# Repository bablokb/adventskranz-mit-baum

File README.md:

Adventskranz mit Baumornament
=============================

In diesem Projekt geht es um einen Adventskranz aus dem 3D-Drucker.
Statt Kerzen kommen Baum-Ornamente zum Einsatz.

3D-Modelle
----------

Das Modell des Baums (`3D/Ornament.stl.gz`) ist von
<https://www.thingiverse.com/thing:2705104>. Mein Remix
(`3D/Ornament-mit-Basis.stl.gz`) fügt einen
kleinen Stamm hinzu sowie ein Loch im Boden. Das dazugehörige
OpenScad-Programm gibt es auch im Verzeichnis `3D`.
N.B: beide STL-Dateien sind mit gzip komprimiert.

Gedruckt ist das Ornament im Vasenmodus mit naturfarbenem PET. Die
Druckdauer beträgt ca. 2 Stunden pro Ornament (0.2mm Schichtdicke).

Der Kranz ist mit OpenScad entworfen und benötigt 6 Stunden Druckzeit.
Zusätzlich gibt es noch Abdeckungen für die Kabelkanäle. Davon
sind vier notwendig, eine Abdeckung hat einen passenden Ausschnitt
für die Kabelzuführung.

Die Toleranzen sind sehr gering, je nach Drucker und Material
ist hier eine Anpassung notwendig. Dank OpenScad ist das auch
ohne große Vorkenntnisse leicht möglich.

Hardware-Setup
--------------

Das Projekt verwendet diffuse 8mm Neopixels von Adafruit, siehe
<https://www.adafruit.com/product/1734>. Ähnliche LEDs gibt es
auch auf eBay. Die Ansteuerung ist i.a.R. gleich, das Pinout
aber nicht.

Jedes Pixel benötigt einen 100nF-Kondensator, das erste Pixel
zusätzlich noch einen 300 Ohm Widerstand in der Datenleitung.

Neopixel benötigen normalerweise 5V (Versorgungsspannung und auf
der Datenleitung). Bei vier Pixel funktioniert es aber i.a.R. auch
mit 3V3. Alle Details zu Neopixel gibt es in dem umfassenden
Handbuch von Adafruit
(<https://learn.adafruit.com/adafruit-neopixel-uberguide>).

Platine
-------

Im Verzeichnis `pcb` gibt es die KiCAD-Quellen für eine passende
Platine. Die Dimensionen der Platine sind exakt auf den Kranz
abgestimmt. Die Miniplatine enthält den Kondensator und den
Widerstand, wobei das Layout so ist, dass die Platine mit oder
ohne Widerstand verwendet werden kann.

Python-Quellen
--------------

Das Verzeichnis `src_python_btn` enthält ein CircuitPython-Programm für
die Steuerung. Das Programm verwendet einen Taster für das Schalten
der LEDs.

Eine Alternativimplementation ist im Verzeichnis `src_python_sr04`.
Hier kommt ein Distanz-Sensor (HC-SR04) statt des Tasters zum Einsatz.

Eine weitere Alternative ist im Verzeichnis `src_python_touch`
vorhanden. Das Beispiel verwendet die direkte Touch-Unterstützung
durch einen Pin des Mikrokontrollers.

Die vom Projekt mitgelieferten Libs sind auf dem 9.x-Stand und mit
Circuit-Python 9.2.0 mit dem Trinket-M0 getestet.

Attiny85-Quellen
----------------

Im Verzeichnis `src_attiny85` gibt es den Quellcode als C-Programm.

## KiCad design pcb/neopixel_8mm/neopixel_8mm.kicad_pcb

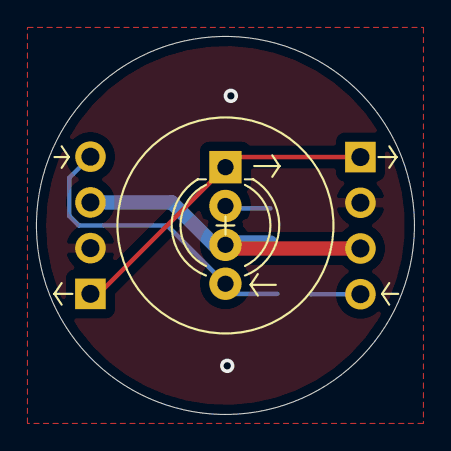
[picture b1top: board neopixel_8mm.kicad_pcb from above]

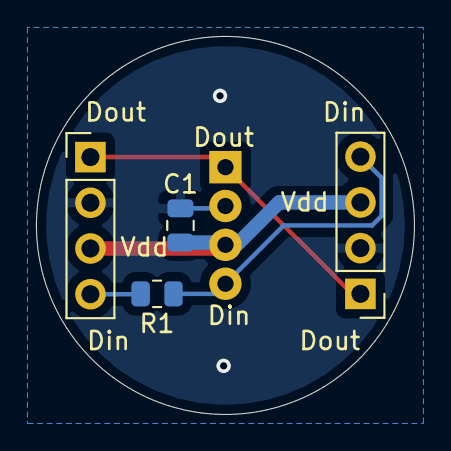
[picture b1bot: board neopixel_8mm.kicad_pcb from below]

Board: 2 copper layers, 21.0 x 21.0 mm, 5 parts (4 on the bottom side), 5 nets.

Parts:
C1: C; C_0805_2012Metric
D1: NeoPixel_THT; LED_D5.0mm-4_RGB_Wide_Pins
J1: Conn_First; PinHeader_1x04_P2.54mm_Vertical
J2: Conn_Next; PinHeader_1x04_P2.54mm_Vertical
R1: R; R_0805_2012Metric

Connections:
GND: C1.2, D1.2, J1.2, J2.2
unnamed: D1.1, J1.1, J2.1
unnamed: D1.4, J2.4, R1.1
unnamed: J1.4, R1.2
VDD: C1.1, D1.3, J1.3, J2.3

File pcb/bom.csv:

Comment,Designator,Footprint,LCSC
"100nF","C1","Capacitor_SMD:C_0805_2012Metric","C49678"
"NeoPixel_THT","D1","LED_THT:LED_D5.0mm-4_RGB_Wide_Pins",""
"Conn_First","J1","Connector_PinHeader_2.54mm:PinHeader_1x04_P2.54mm_Vertical",""
"Conn_Next","J2","Connector_PinHeader_2.54mm:PinHeader_1x04_P2.54mm_Vertical",""
"300Ω","R1","Resistor_SMD:R_0805_2012Metric","C17617"

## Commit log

2021-08-21 added vscode-files
2021-08-21 added text
2021-08-21 translated to German
2021-08-31 added some comments
2021-08-31 fixed reference to stl
2021-09-04 pack stl in zip
2021-09-04 document stl within zip
2021-09-07 added cover
2021-09-09 fixed postion of cutout on cover
2021-09-11 replaced zip-version with gzip version
2021-09-11 compress file
2021-09-11 updated project-url
2021-09-20 optimzed cover
2021-09-20 added some details
2021-09-22 updated to 7.x-library bundle
2021-09-22 add section about SR-HC04 implementation
2021-09-23 code cleanup
2021-09-25 link to new images
2021-09-30 bugfix: remove delay during idle
2021-11-05 changed variables from int to byte
2021-11-05 changed debounce-delay to 300ms
2021-11-05 save current counter to eeprom
2021-11-18 reduced y-offset for attiny85
2021-11-18 sd-cutout 1mm lower
2021-11-18 increased x-dim for attiny85 by 0.3mm
2021-11-24 fixed cutout sizes and offsets
2021-11-27 added macro for distance-check, set to 30cm
2024-11-16 added python touch-control example
2024-11-16 renamed src_python to src_python_btn
2024-11-16 added boot_out.txt
2024-11-16 upgraded to 9.x library files
2024-11-16 fixed markup
2024-11-19 blink board-LED when touch detected
2024-11-19 updated for Pimoroni Plasma2040
2024-11-19 exclude stl-files
2024-11-19 case for Trinket-M0
2024-11-21 start with random color, color transition after 5 secs
2024-11-21 implement gamma correction
2024-11-21 support second button to change brightness
2024-11-27 change implementation of first (random) color
